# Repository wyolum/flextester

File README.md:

# flextester
forked from Drew Fustini's https://github.com/oshpark/flextester

License
-------
[CERN Open Hardware Licence v1.2 ]

[CERN Open Hardware Licence v1.2 ]:http://www.ohwr.org/attachments/2388/cern_ohl_v_1_2.txt

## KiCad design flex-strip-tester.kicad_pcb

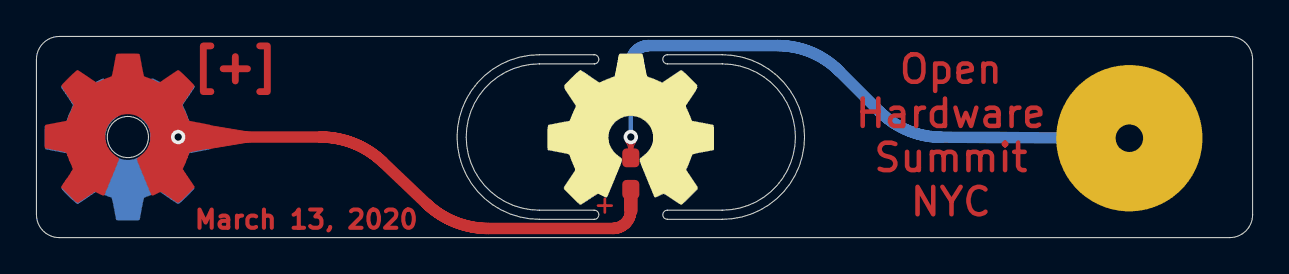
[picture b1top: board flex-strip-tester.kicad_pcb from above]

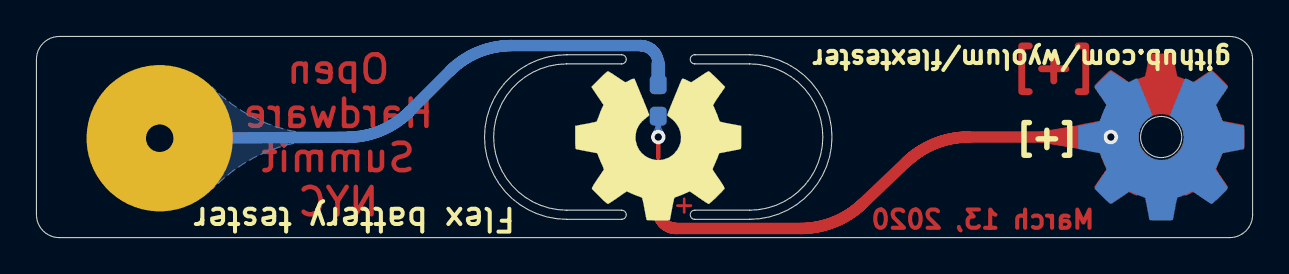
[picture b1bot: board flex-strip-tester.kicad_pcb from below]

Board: 2 copper layers, 67.6 x 11.2 mm, 7 parts (3 on the bottom side), 3 nets.

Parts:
D1: LED; LED_0603_1608Metric_Pad1.05x0.95mm_HandSolder
J1, J5: Logo; OSHW-Logo2_14.6x12mm_SilkScreen
J2, J4: [+]; OSHW-Logo2_14.6x12mm_Pad
J3: [-]; TestPoint_Pad_4.0x4.0mm
R1: R; R_0603_1608Metric_Pad1.05x0.95mm_HandSolder

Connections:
+3V3: D1.2, J2.1, J4.1
GND: J3.1, R1.2
unnamed: D1.1, R1.1

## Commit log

2020-03-13 flextester with strain relief cuts
